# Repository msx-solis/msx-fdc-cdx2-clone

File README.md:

# msx-fdc-cdx2-clone
MSX compatible I/O Port Based Floppy Disk Controller interface.

Please, continue reading at the following link for building instructions:

https://github.com/msx-solis/msx-fdc-cdx2-clone/blob/main/cdx-2-iface2.4/doc/README.md

Special thanks to Paulo Maluf, XaviRompe, Andortizg and konkotgit.

Similar project and additional info at:

https://github.com/konkotgit/fdd-cdx2

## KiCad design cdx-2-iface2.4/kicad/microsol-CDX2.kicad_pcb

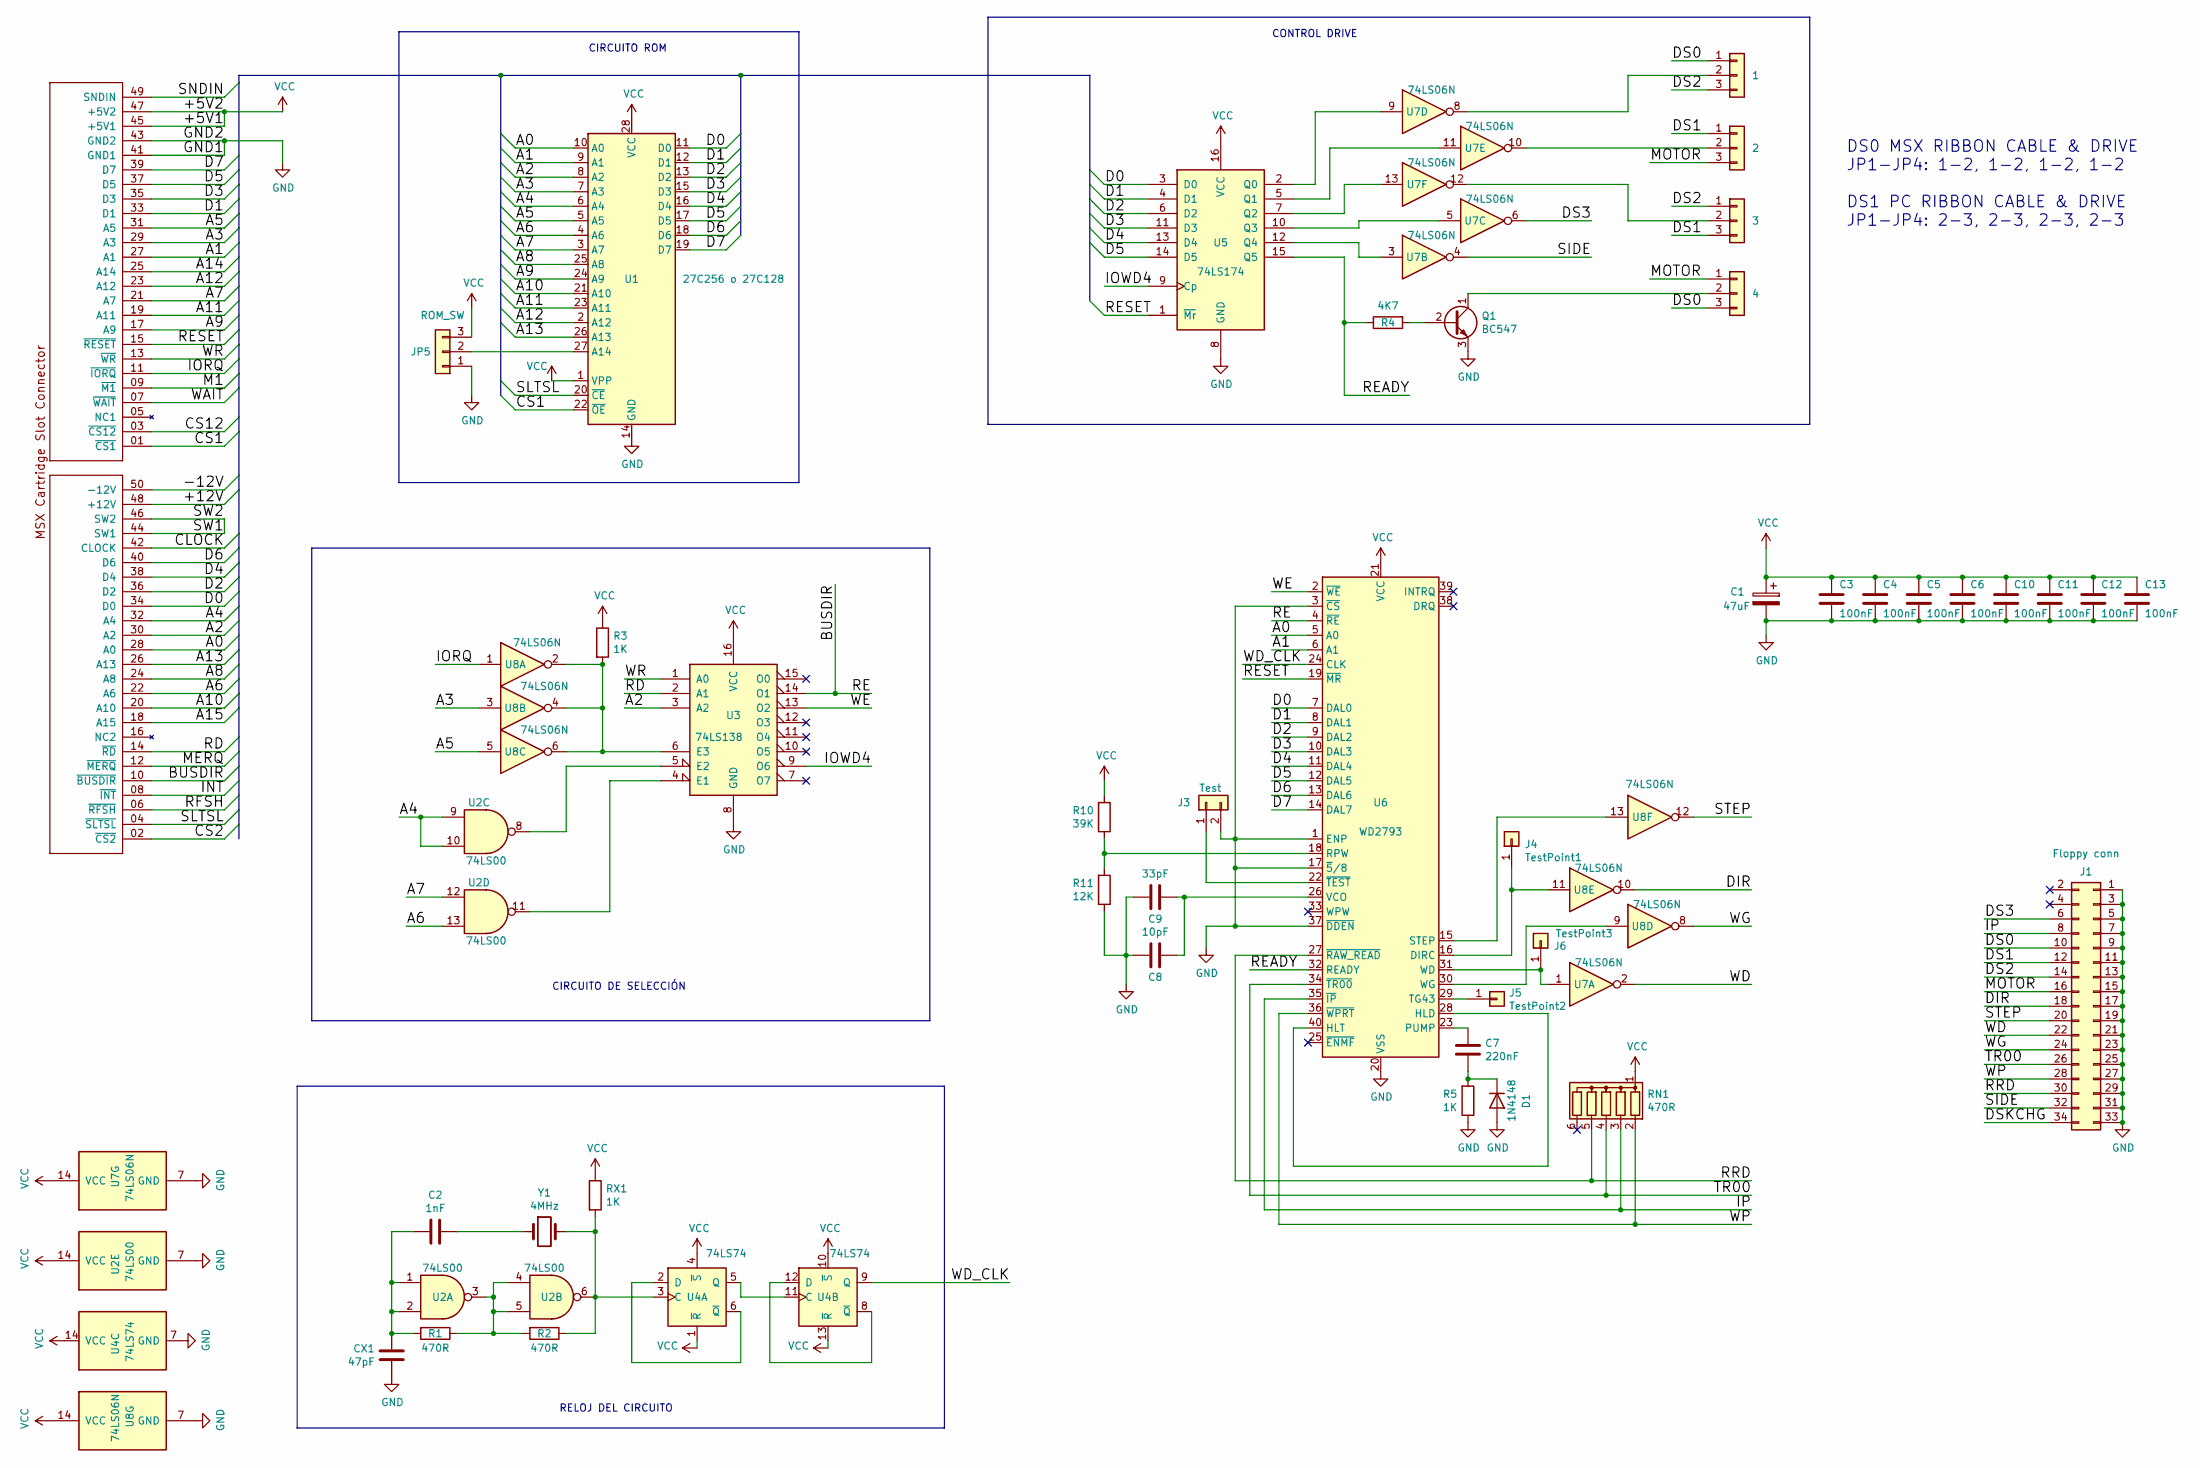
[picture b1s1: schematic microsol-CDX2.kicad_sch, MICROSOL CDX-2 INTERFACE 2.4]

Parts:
1: DS0-sel; PinHeader_1x03_P2.54mm_Vertical
2: DS1-sel; PinHeader_1x03_P2.54mm_Vertical
3: DS2-sel; PinHeader_1x03_P2.54mm_Vertical
4: MOTOR-sel; PinHeader_1x03_P2.54mm_Vertical
C1: 47uF; CP_Radial_D6.3mm_P2.50mm
C2: 1nF; C_Disc_D4.7mm_W2.5mm_P5.00mm
C3, C4, C5, C6, C10, C11, C12, C13: 100nF; C_Disc_D4.7mm_W2.5mm_P5.00mm
C7: 220nF; C_Disc_D4.7mm_W2.5mm_P5.00mm
C8: 10pF; C_Disc_D4.7mm_W2.5mm_P5.00mm
C9: 33pF; C_Disc_D4.7mm_W2.5mm_P5.00mm
CX1: 47pF; C_Disc_D4.7mm_W2.5mm_P5.00mm
D1: 1N4148; D_DO-35_SOD27_P7.62mm_Horizontal
J1: Floppy conn; PinHeader_2x17_P2.54mm_Horizontal
J2: MSX_SLOT_CON; CARTRIDGE_#_MSX_XL
J3: Test; PinHeader_1x02_P2.54mm_Vertical
J4: TestPoint1; PinSocket_1x01_P2.54mm_Vertical
J5: TestPoint2; PinSocket_1x01_P2.54mm_Vertical
J6: TestPoint3; PinSocket_1x01_P2.54mm_Vertical
JP5: ROM_SW; PinHeader_1x03_P2.54mm_Vertical
Q1: BC547; TO-92_Inline
R1, R2: 470R; R_Axial_DIN0207_L6.3mm_D2.5mm_P7.62mm_Horizontal
R3, R5: 1K; R_Axial_DIN0207_L6.3mm_D2.5mm_P7.62mm_Horizontal
R4: 4K7; R_Axial_DIN0207_L6.3mm_D2.5mm_P7.62mm_Horizontal
R10: 39K; R_Axial_DIN0207_L6.3mm_D2.5mm_P7.62mm_Horizontal
R11: 12K; R_Axial_DIN0207_L6.3mm_D2.5mm_P7.62mm_Horizontal
RN1: 470R; R_Array_SIP6
RX1: 1K; R_Axial_DIN0207_L6.3mm_D2.5mm_P7.62mm_Horizontal
U1: 27C256 o 27C128; DIP-28c_W15.24mm_Socket_LongPads
U2: 74LS00; DIP-14c_W7.62mm_LongPads
U3: 74LS138; DIP-16c_W7.62mm_Socket_LongPads
U4: 74LS74; DIP-14c_W7.62mm_LongPads
U5: 74LS174; DIP-16c_W7.62mm_Socket_LongPads
U6: WD2793; DIP-40c_W15.24mm_LongPads
U7, U8: 74LS06N; DIP-14c_W7.62mm_LongPads
Y1: 4MHz; Crystal_HC49-U_Vertical

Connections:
/+12V: J2.48 (+12V)
/-12V: J2.50 (-12V)
/A0: J2.28 (A0), U1.10 (A0), U6.5 (A0)
/A1: J2.27 (A1), U1.9 (A1), U6.6 (A1)
/A2: J2.30 (A2), U1.8 (A2), U3.3 (A2)
/A3: J2.29 (A3), U1.7 (A3), U8.3
/A4: J2.32 (A4), U1.6 (A4), U2.9, U2.10
/A5: J2.31 (A5), U1.5 (A5), U8.5
/A6: J2.22 (A6), U1.4 (A6), U2.13
/A7: J2.21 (A7), U1.3 (A7), U2.12
/A8: J2.24 (A8), U1.25 (A8)
/A9: J2.17 (A9), U1.24 (A9)
/A10: J2.20 (A10), U1.21 (A10)
/A11: J2.19 (A11), U1.23 (A11)
/A12: J2.23 (A12), U1.2 (A12)
/A13: J2.26 (A13), U1.26 (A13)
/A14: J2.25 (A14)
/A15: J2.18 (A15)
/BUSDIR: J2.10 (~BUSDIR), U3.14 (O1), U6.4 (~RE)
/CLOCK: J2.42 (CLOCK)
/CS1: J2.01 (~CS1), U1.22 (~OE)
/CS2: J2.02 (~CS2)
/CS12: J2.03 (~CS12)
/D0: J2.34 (D0), U1.11 (D0), U5.3 (D0), U6.7 (DAL0)
/D1: J2.33 (D1), U1.12 (D1), U5.4 (D1), U6.8 (DAL1)
/D2: J2.36 (D2), U1.13 (D2), U5.6 (D2), U6.9 (DAL2)
/D3: J2.35 (D3), U1.15 (D3), U5.11 (D3), U6.10 (DAL3)
/D4: J2.38 (D4), U1.16 (D4), U5.13 (D4), U6.11 (DAL4)
/D5: J2.37 (D5), U1.17 (D5), U5.14 (D5), U6.12 (DAL5)
/D6: J2.40 (D6), U1.18 (D6), U6.13 (DAL6)
/D7: J2.39 (D7), U1.19 (D7), U6.14 (DAL7)
/DIR: J1.18, U8.10
/DS0: 1.1, 4.3, J1.10
/DS1: 2.1, 3.3, J1.12
/DS2: 1.3, 3.1, J1.14
/DS3: J1.6, U7.6
/DSKCHG: J1.34
/INT: J2.08 (~INT)
/IORQ: J2.11 (~IORQ), U8.1
/IOWD4: U3.9 (O6), U5.9 (Cp)
/IP: J1.8, RN1.3 (R2), U6.35 (~IP)
/M1: J2.09 (~M1)
/MERQ: J2.12 (~MERQ)
/MOTOR: 2.3, 4.1, J1.16
/RD: J2.14 (~RD), U3.2 (A1)
/READY: R4.1, U5.15 (Q5), U6.32 (READY)
/RESET: J2.15 (~RESET), U5.1 (~Mr), U6.19 (~MR)
/RFSH: J2.06 (~RFSH)
/RRD: J1.30, RN1.5 (R4), U6.27 (~RAW_READ)
/SIDE: J1.32, U7.4
/SLTSL: J2.04 (~SLTSL), U1.20 (~CE)
/SNDIN: J2.49 (SNDIN)
/STEP: J1.20, U8.12
/SW1: J2.44 (SW1), J2.46 (SW2)
/TR00: J1.26, RN1.4 (R3), U6.34 (~TR00)
/WAIT: J2.07 (~WAIT)
/WD: J1.22, U7.2
/WD_CLK: U4.9 (Q), U6.24 (CLK)
/WE: U3.13 (O2), U6.2 (~WE)
/WG: J1.24, U8.8
/WP: J1.28, RN1.2 (R1), U6.36 (~WPRT)
/WR: J2.13 (~WR), U3.1 (A0)
GND: C1.2, C3.2, C4.2, C5.2, C6.2, C8.2, C9.1, C10.2, C11.2, C12.2, C13.2, CX1.1, D1.2 (A), J1.1, J1.3, J1.5, J1.7, J1.9, J1.11, J1.13, J1.15, J1.17, J1.19, J1.21, J1.23, J1.25, J1.27, J1.29, J1.31, J1.33, J2.41 (GND1), J2.43 (GND2), J3.2, JP5.1, Q1.3 (E), R5.1, R11.1, U1.14 (GND), U2.7 (GND), U3.8 (GND), U4.7 (GND), U5.8 (GND), U6.1 (ENP), U6.3 (~CS), U6.17 (~5/8), U6.20 (VSS), U6.37 (~DDEN), U7.7 (GND), U8.7 (GND)
unnamed: C2.1, Y1.1
unnamed: C2.2, CX1.2, R1.2, U2.1, U2.2
unnamed: C7.1, U6.23 (PUMP)
unnamed: C7.2, D1.1 (K), R5.2
unnamed: C8.1, C9.2, U6.26 (VCO)
unnamed: J3.1, U6.22 (~TEST)
unnamed: J4.1, U6.16 (DIRC), U8.11
unnamed: J5.1, U6.29 (TG43)
unnamed: J6.1, U6.31 (WD), U7.1
unnamed: 1.2, U7.8
unnamed: 2.2, U7.10
unnamed: 3.2, U7.12
unnamed: 4.2, Q1.1 (C)
unnamed: JP5.2, U1.27 (A14)
unnamed: Q1.2 (B), R4.2
unnamed: R1.1, R2.2, U2.3, U2.4, U2.5
unnamed: R2.1, RX1.2, U2.6, U4.3 (C), Y1.2
unnamed: R3.2, U3.6 (E3), U8.2, U8.4, U8.6
unnamed: R10.1, R11.2, U6.18 (RPW)
unnamed: U2.8, U3.5 (E2)
unnamed: U2.11, U3.4 (E1)
unnamed: U4.2 (D), U4.6 (~Q)
unnamed: U4.5 (Q), U4.11 (C)
unnamed: U4.8 (~Q), U4.12 (D)
unnamed: U5.2 (Q0), U7.9
unnamed: U5.5 (Q1), U7.11
unnamed: U5.7 (Q2), U7.13
unnamed: U5.10 (Q3), U7.5
unnamed: U5.12 (Q4), U7.3
unnamed: U6.15 (STEP), U8.13
unnamed: U6.28 (HLD), U6.40 (HLT)
unnamed: U6.30 (WG), U8.9
VCC: C1.1, C3.1, C4.1, C5.1, C6.1, C10.1, C11.1, C12.1, C13.1, J2.45 (+5V1), J2.47 (+5V2), JP5.3, R3.1, R10.2, RN1.1 (common), RX1.1, U1.1 (VPP), U1.28 (VCC), U2.14 (VCC), U3.16 (VCC), U4.1 (~R), U4.4 (~S), U4.10 (~S), U4.13 (~R), U4.14 (VCC), U5.16 (VCC), U6.21 (VCC), U7.14 (VCC), U8.14 (VCC)

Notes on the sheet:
CIRCUITO DE SELECCIÓN
RELOJ DEL CIRCUITO
CONTROL DRIVE
CIRCUITO ROM
DS0 MSX RIBBON CABLE & DRIVE JP1-JP4: 1-2, 1-2, 1-2, 1-2 DS1 PC RIBBON CABLE & DRIVE JP1-JP4: 2-3, 2-3, 2-3, 2-3

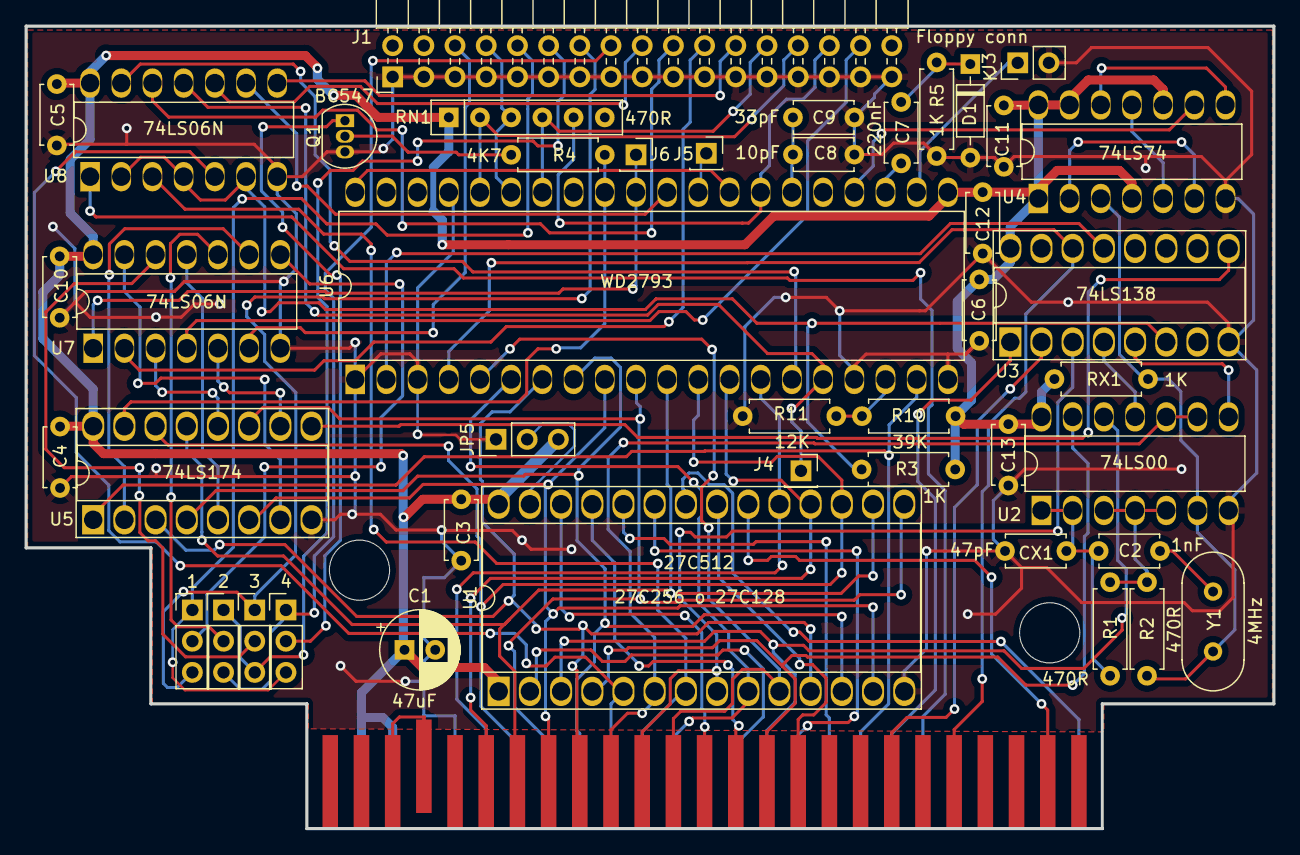
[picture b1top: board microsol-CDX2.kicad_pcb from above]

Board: 2 copper layers, 101.6 x 65.3 mm, 45 parts (0 on the bottom side), 82 nets.
